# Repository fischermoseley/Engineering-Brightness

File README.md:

# Engineering-Brightness
1.3 billion people across the world lack a source of artificial lighting, and are unable to safely leave thier homes or do work after dark. Often a rudimentary kerosene lamp is used, but carbon monoxide and combustion byproducts build up in the air, leading to death in some cases. Kerosene is also very expensive, and provides little useful light. 

Engineering Brightnes is a program designed to provide free, safe, and reliable artifical lighting to the world. 

Originally started at Preston Middle School, Colorado Early Colleges Fort Collins is currently prototyping a new design, and the files are available here. The electrical system has been sucessfully prototyped, and the mechanical enclosure is currently under development.

More information is available at http://philanthropic-engineering.org/

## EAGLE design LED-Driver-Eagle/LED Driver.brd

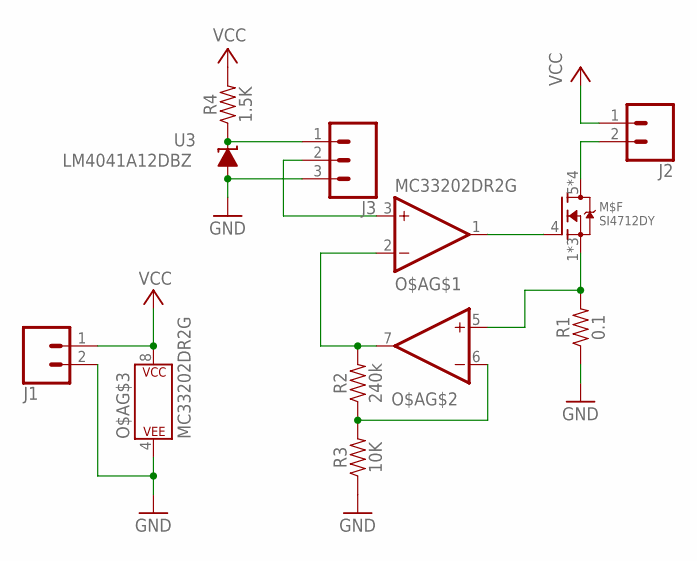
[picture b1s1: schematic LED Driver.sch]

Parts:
J1, J2: CONN_02PTH4; 1X02_XTRA_BIG
J3: CONN_03; 1X03
M$F: SI4712DY; SO8
O$A: MC33202DR2G; SOIC8
R1: 0.1; 1210
R2: 240k; 0603
R3: 10K; 0603
R4: 1.5K; 0603
U3: LM4041A12DBZ; DBZ_R-PDSO-G3

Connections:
GND: J1.2, J3.3, O$A.4 (P$V-), R1.1, R3.1, U3.2 (A)
unnamed: J3.1, R4.1, U3.1 (C)
unnamed: J3.2, O$A.3 (+IN)
unnamed: M$F.4 (G), O$A.1 (OUT)
unnamed: J2.2, M$F.5 (D), M$F.6 (D), M$F.7 (D), M$F.8 (D)
unnamed: M$F.1 (S), M$F.2 (S), M$F.3 (S), O$A.5 (+IN), R1.2
unnamed: O$A.2 (-IN), O$A.7 (OUT), R2.2
unnamed: O$A.6 (-IN), R2.1, R3.2
VCC: J1.1, J2.1, O$A.8 (P$V+), R4.2

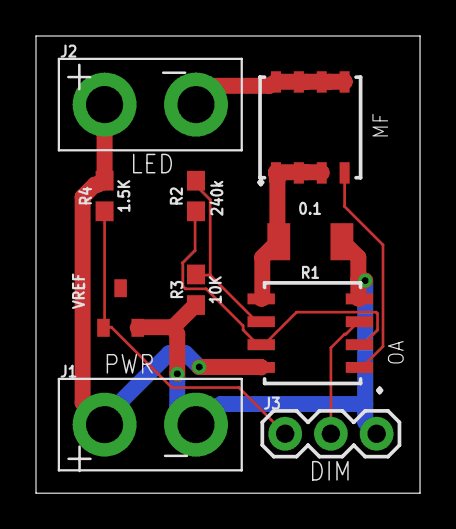
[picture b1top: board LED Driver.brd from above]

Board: 2 copper layers, 21.3 x 25.4 mm, 10 parts (0 on the bottom side), 9 nets.

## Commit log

2018-03-02 Added gerbers sent to OSHPark
2018-03-22 Final Push of V1 before V2
2018-03-23 Updated BOM for Revision B
2018-03-23 Added LED Comparison Chart
2018-03-23 Updated LED Driver BOM
    Forgot that the output connector is supplied by RapidLED
2018-03-26 Fixed board asthetics
    Added labels for input terminals, fixed logo, changed text to Revision B
2018-03-26 Reordered file structure
    Added folders for eagle files, fixed readme, deleted unnecessary file
2018-03-26 Added Gerbers
    Processes using OSHpark 2-layer
2018-03-26 Fixed gerbers
    Accidentally zipped a folder containing the files, not the files themselves
2018-03-27 Fixed Gerbers
    CAM job wasn't processed with OSHpark processor, switched to thier 2 layer
2018-03-27 Added U3 Label
    Added label for U3 (vref) and updated gerbers
2018-03-27 Added CECFC on bottom of board
2018-03-27 Pushed to Fusion
2018-03-30 Changed U1 and U2 to MF and OA
    Updated Gerbers and eagle board files
2018-04-10 Added QC/Troubleshooting guide
    With pictures!
2018-04-10 Removed MS word temp files
2018-04-16 Removed spurious gerbers
2018-04-16 Changed wording
2018-04-25 Added Cameo file for cutting the stencil
    Actual size, doesn't need to be rescaled.
2018-04-25 Added DXF for the stencil
2018-04-25 Reorganized stencil files
2018-05-24 Added solar panel case and mylar cutout
2018-05-24 Added description
2018-05-24 Revert "Added description"
    This reverts commit 234bd5fb7c7e8e3c49daa0cfb30cb09e909068a3.

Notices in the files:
parts and their libraries:
SparkFun-Resistors: Licensing: Creative Commons ShareAlike 4.0 International - https://creativecommons.org/licenses/by-sa/4.0
